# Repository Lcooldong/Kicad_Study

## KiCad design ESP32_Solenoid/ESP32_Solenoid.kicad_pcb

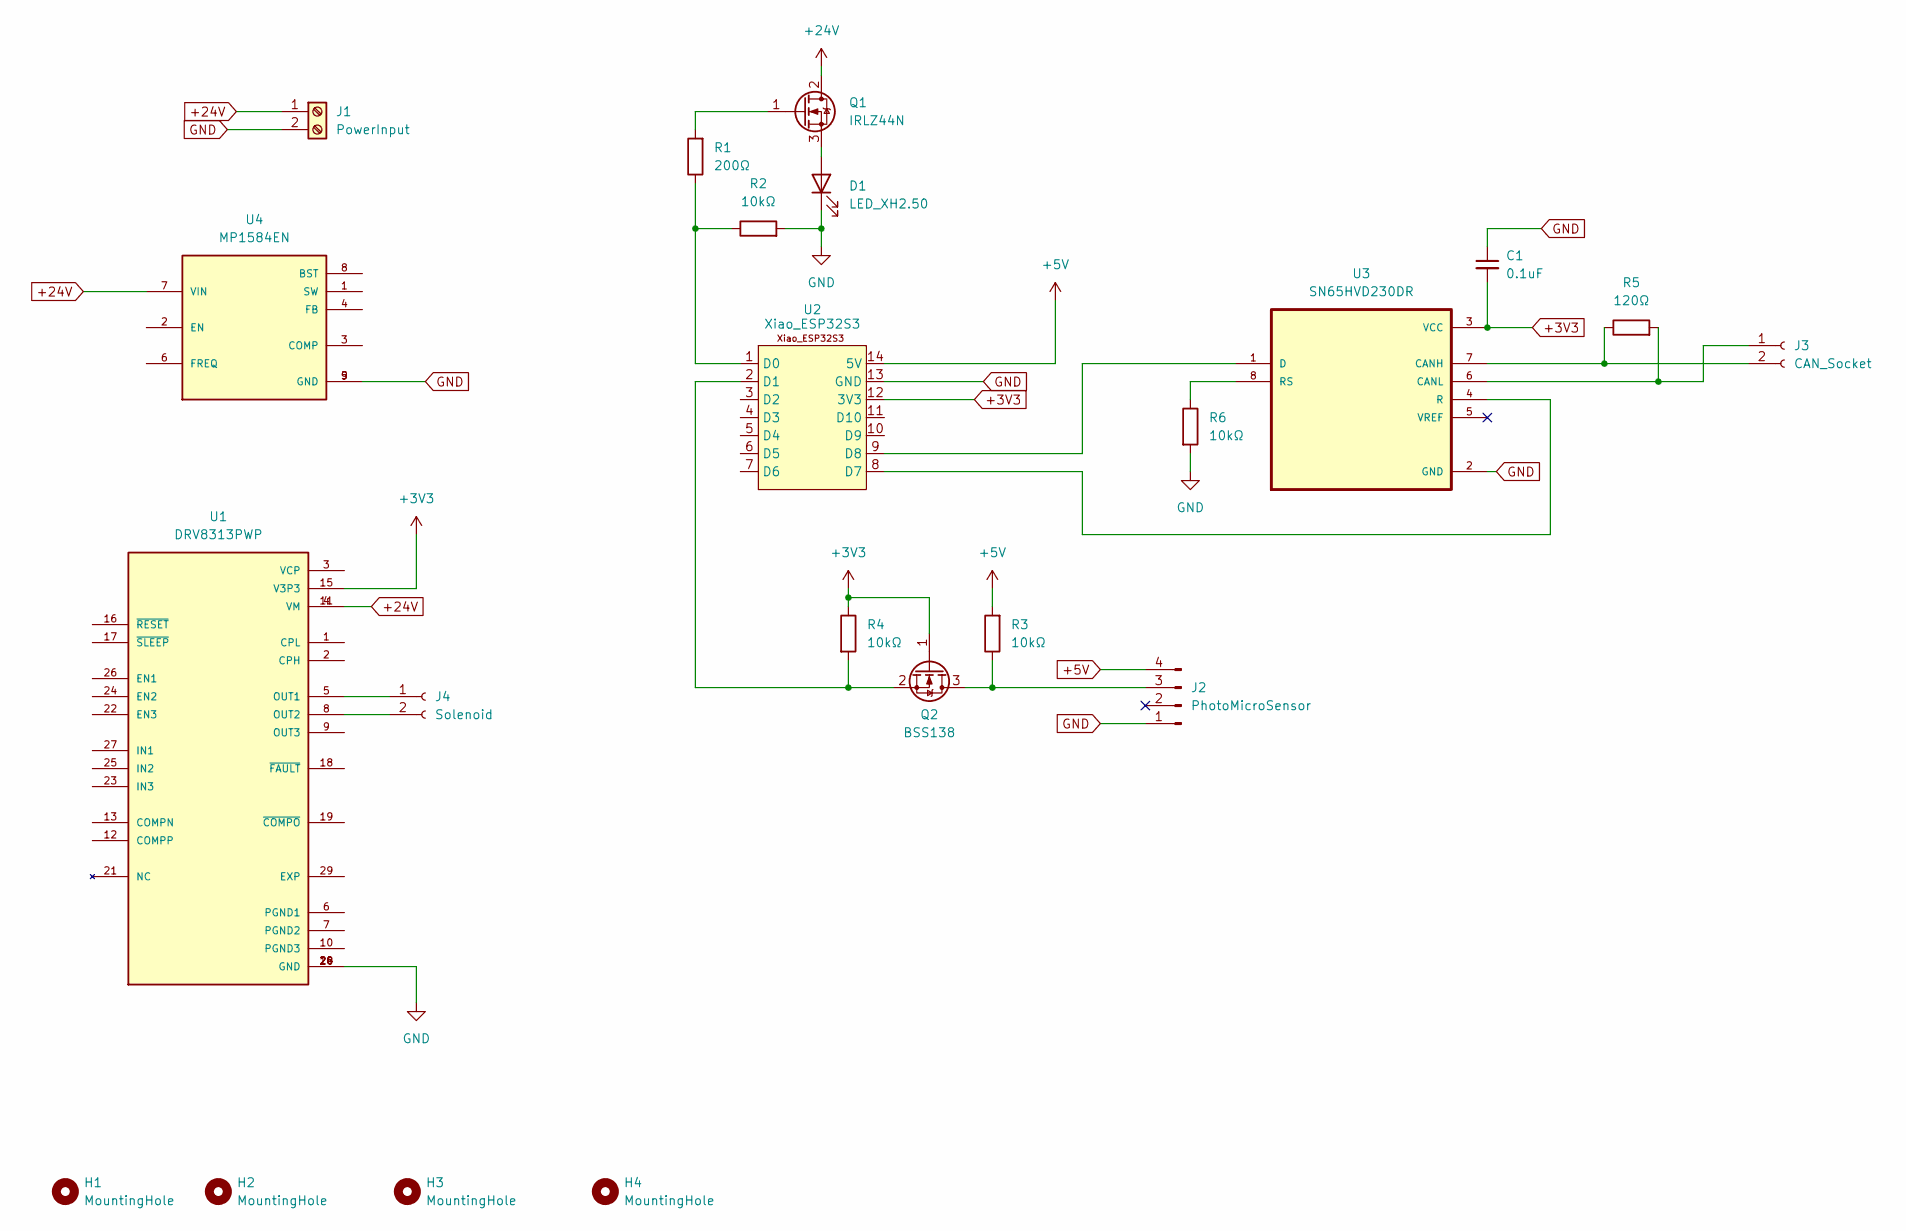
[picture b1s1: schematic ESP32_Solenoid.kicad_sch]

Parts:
C1: 0.1uF; C_1206_3216Metric
D1: LED_XH2.50; JST_XH_B2B-XH-A_1x02_P2.50mm_Vertical
H1, H2, H3, H4: MountingHole; MountingHole_3.2mm_M3_Pad_Via
J1: PowerInput; TerminalBlock_Phoenix_MKDS-1,5-2-5.08_1x02_P5.08mm_Horizont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
J2: PhotoMicroSensor; JST_XH_B4B-XH-A_1x04_P2.50mm_Vertical
J3: CAN_Socket; TerminalBlock_Phoenix_MKDS-1,5-2-5.08_1x02_P5.08mm_Horizont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
J4: Solenoid; TerminalBlock_Phoenix_MKDS-1,5-2-5.08_1x02_P5.08mm_Horizont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
Q1: IRLZ44N; IRLZ44NSTRLPBF
Q2: BSS138; SOT-23
R1: 200Ω; R_1206_3216Metric
R2, R3, R4, R6: 10kΩ; R_1206_3216Metric
R5: 120Ω; R_0805_2012Metric
U1: DRV8313PWP; SOP65P640X120-29N; PARTREV D; DigiKey_Part_Number 296-35540-5-ND
U2: Xiao_ESP32S3; Xiao_ESP32S3_THT
U3: SN65HVD230DR; SN65HVD230DR_SOIC127P599X175-8N
U4: MP1584EN; SOIC127P600X170-9N

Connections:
+3V3: C1.2, Q2.1 (G), R4.1, U1.15 (V3P3), U2.12 (3V3), U3.3 (VCC)
+5V: J2.4, R3.2, U2.14 (5V)
+24V: J1.1, Q1.2 (D), U1.4 (VM), U1.11 (VM), U4.7 (VIN)
GND: C1.1, D1.1 (K), J1.2, J2.1, R2.2, R6.2, U1.14 (GND), U1.20 (GND), U1.28 (GND), U2.13 (GND), U3.2 (GND), U4.5 (GND), U4.9 (GND)
unnamed: D1.2 (A), Q1.3 (S)
unnamed: J2.3, Q2.3 (D), R3.1
unnamed: J3.1, R5.2, U3.6 (CANL)
unnamed: J3.2, R5.1, U3.7 (CANH)
unnamed: J4.1, U1.5 (OUT1)
unnamed: J4.2, U1.8 (OUT2)
unnamed: Q1.1 (G), R1.2
unnamed: Q2.2 (S), R4.2, U2.2 (D1)
unnamed: R1.1, R2.1, U2.1 (D0)
unnamed: U2.8 (D7), U3.4 (R)
unnamed: U2.9 (D8), U3.1 (D)
unnamed: R6.1, U3.8 (RS)

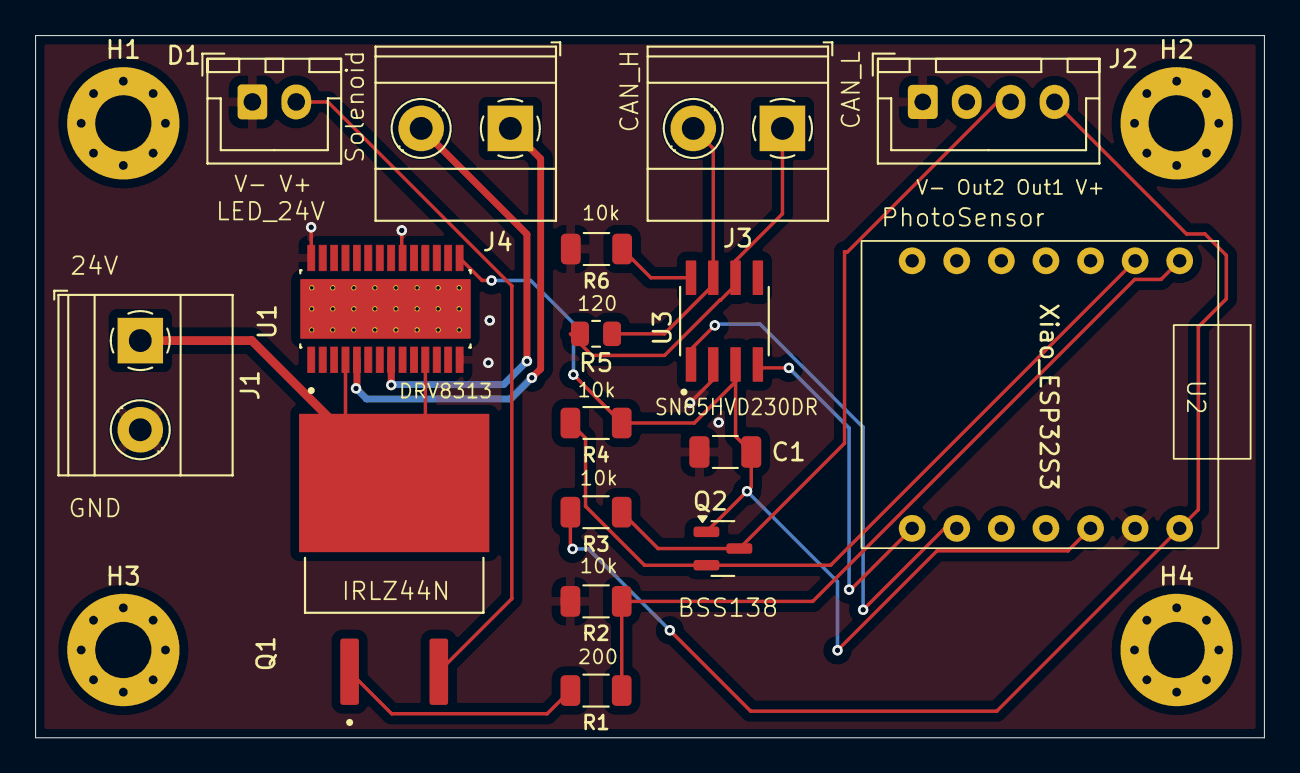
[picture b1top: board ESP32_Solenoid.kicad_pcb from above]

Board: 2 copper layers, 70.0 x 40.0 mm, 21 parts (0 on the bottom side), 16 nets.

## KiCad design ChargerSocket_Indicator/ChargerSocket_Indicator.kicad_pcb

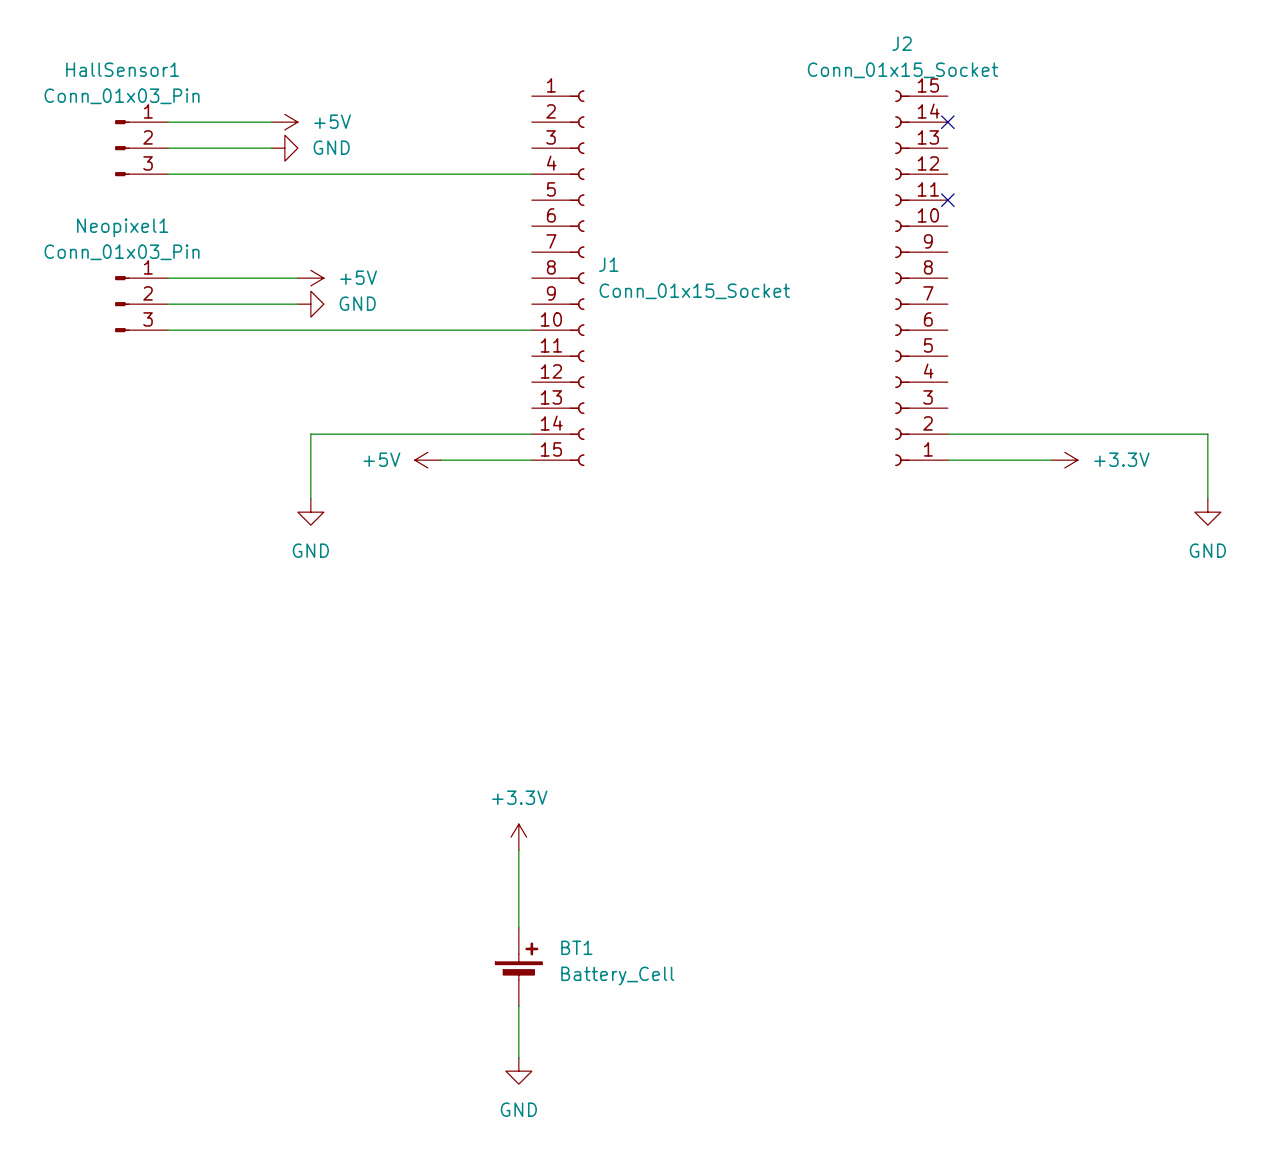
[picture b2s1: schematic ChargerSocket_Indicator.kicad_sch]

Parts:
BT1: Battery_Cell; SolderWire-0.1sqmm_1x02_P3.6mm_D0.4mm_OD1mm_Relief
HallSensor1: Conn_01x03_Pin; PinHeader_1x03_P2.54mm_Vertical
J1, J2: Conn_01x15_Socket; PinSocket_1x15_P2.54mm_Vertical
Neopixel1: Conn_01x03_Pin; PinHeader_1x03_P2.54mm_Vertical

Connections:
+3.3V: BT1.1 (+), J2.1
+5V: HallSensor1.1, J1.15, Neopixel1.1
GND: BT1.2 (-), HallSensor1.2, J1.14, J2.2, Neopixel1.2
unnamed: HallSensor1.3, J1.4
unnamed: J1.10, Neopixel1.3

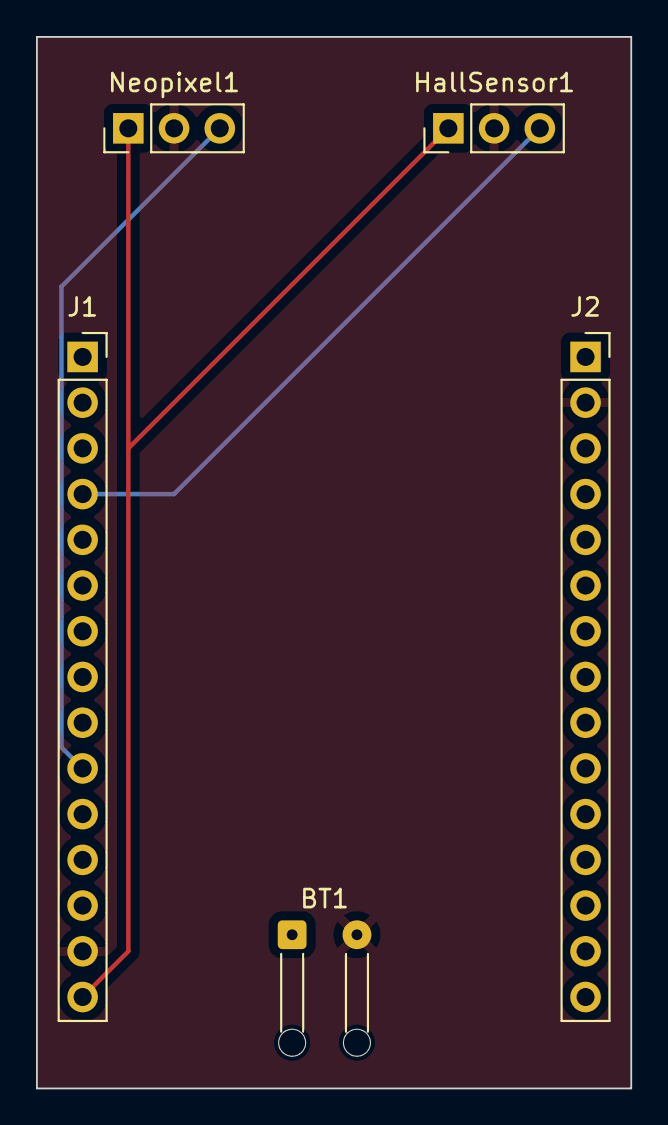
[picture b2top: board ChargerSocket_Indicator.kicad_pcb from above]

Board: 2 copper layers, 33.0 x 58.4 mm, 5 parts (0 on the bottom side), 5 nets.

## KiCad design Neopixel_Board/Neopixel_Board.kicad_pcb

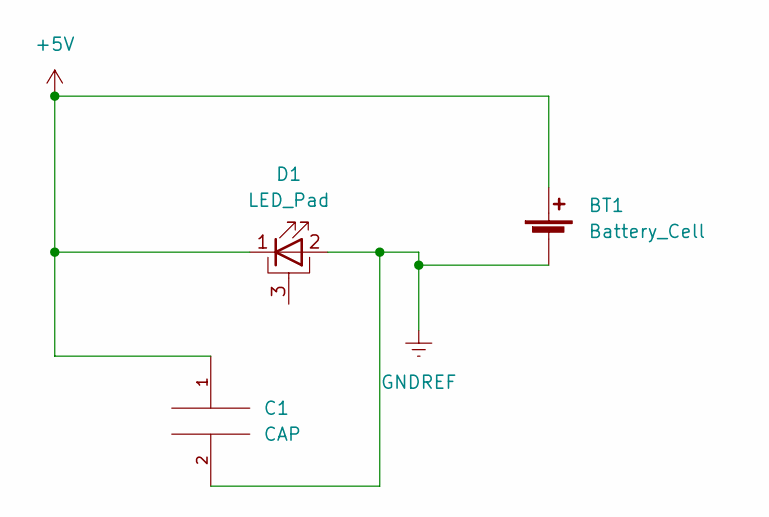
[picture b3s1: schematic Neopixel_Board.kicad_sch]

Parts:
BT1: Battery_Cell; Banana_Jack_2Pin
C1: CAP; CP_Elec_5x3
D1: LED_Pad; LED_WS2812B_PLCC4_5.0x5.0mm_P3.2mm

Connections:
+5V: BT1.1 (+), C1.1, D1.1 (K)
GNDREF: BT1.2 (-), C1.2, D1.2 (A)

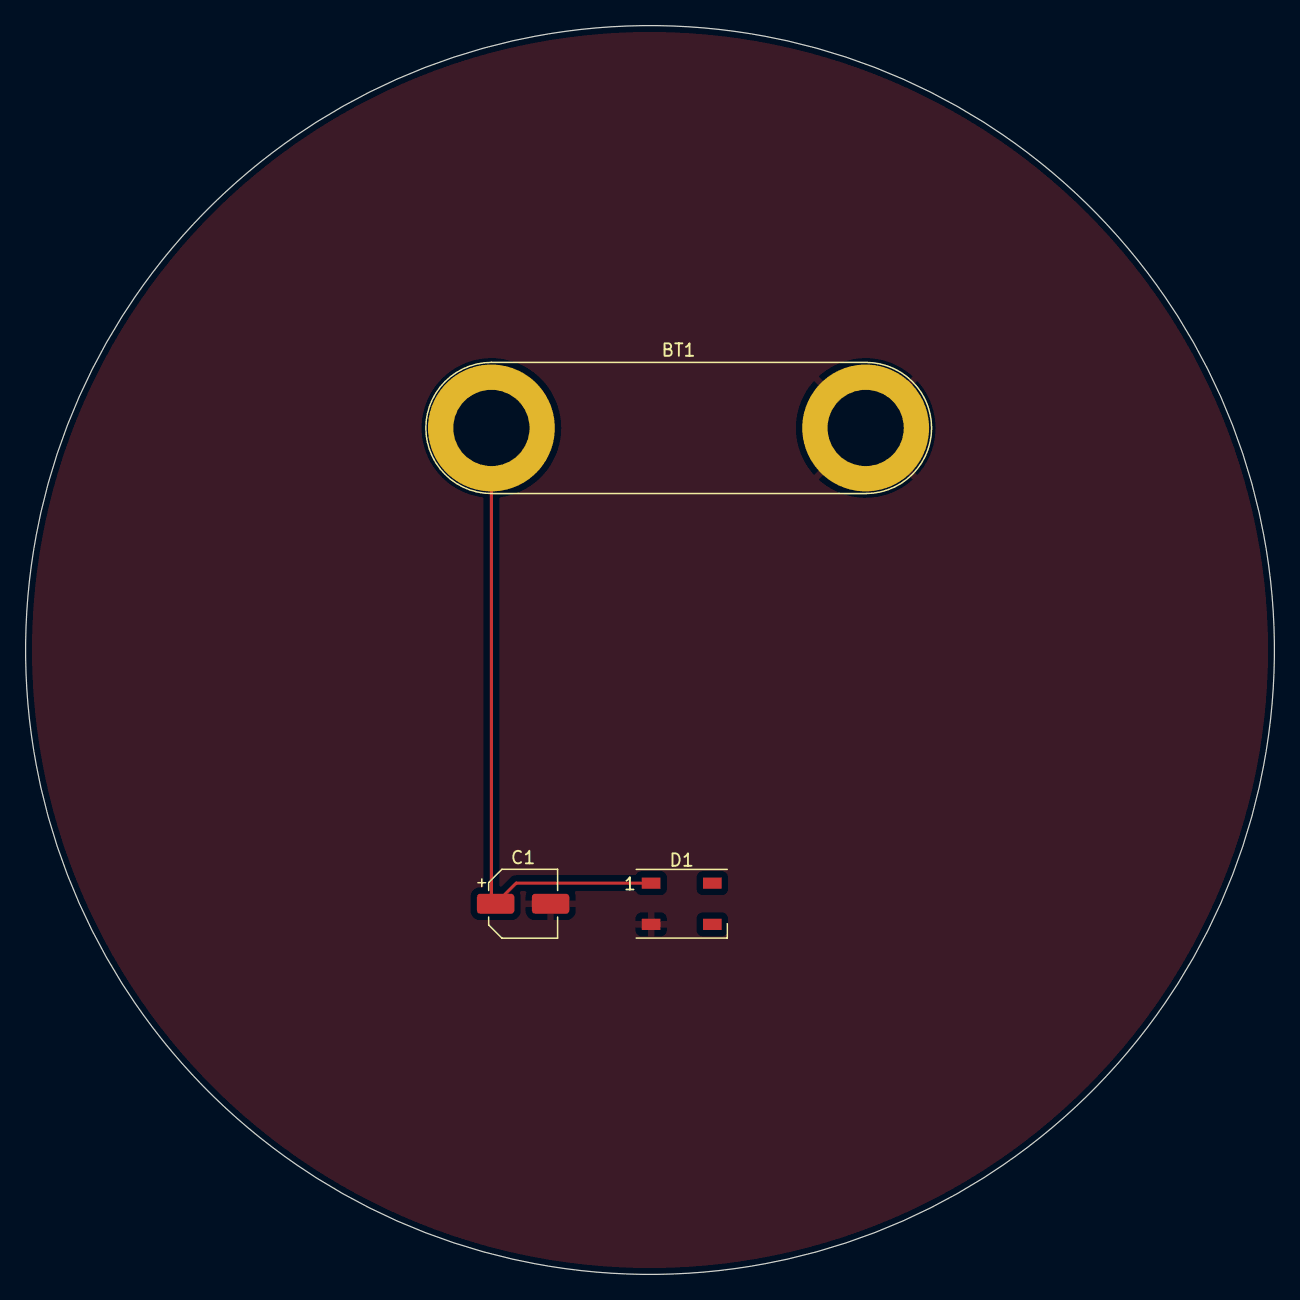
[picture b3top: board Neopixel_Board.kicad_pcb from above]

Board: 2 copper layers, 100.0 x 100.0 mm, 3 parts (0 on the bottom side), 2 nets.

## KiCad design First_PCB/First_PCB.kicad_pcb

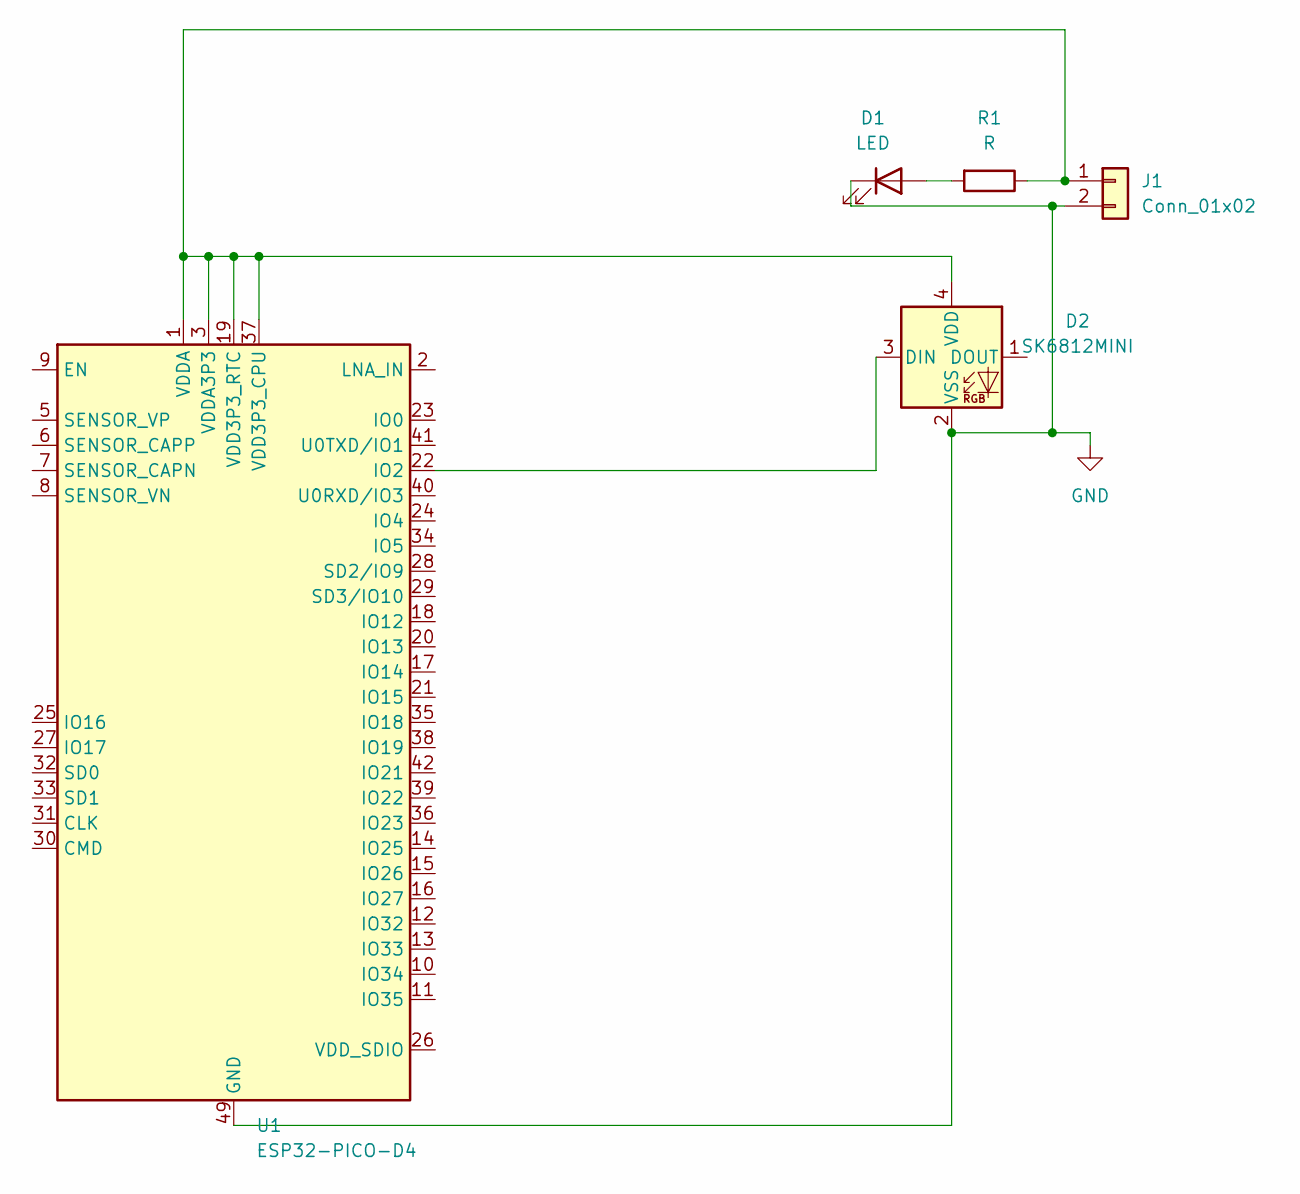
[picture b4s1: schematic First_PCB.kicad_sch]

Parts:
D1: LED; LED_1W_3W_R8
D2: SK6812MINI; LED_SK6812MINI_PLCC4_3.5x3.5mm_P1.75mm
J1: Conn_01x02; PinSocket_1x02_P2.54mm_Vertical
R1: R; R_0603_1608Metric
U1: ESP32-PICO-D4; QFN-48-1EP_7x7mm_P0.5mm_EP5.3x5.3mm

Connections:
GND: D1.1 (K), D2.2 (VSS), J1.2, U1.49 (GND)
unnamed: D1.2 (A), R1.2
unnamed: D2.3 (DIN), U1.22 (IO2)
unnamed: D2.4 (VDD), J1.1, R1.1, U1.1 (VDDA), U1.3 (VDDA3P3), U1.4 (VDDA3P3), U1.19 (VDD3P3_RTC), U1.37 (VDD3P3_CPU), U1.43 (VDDA), U1.46 (VDDA)

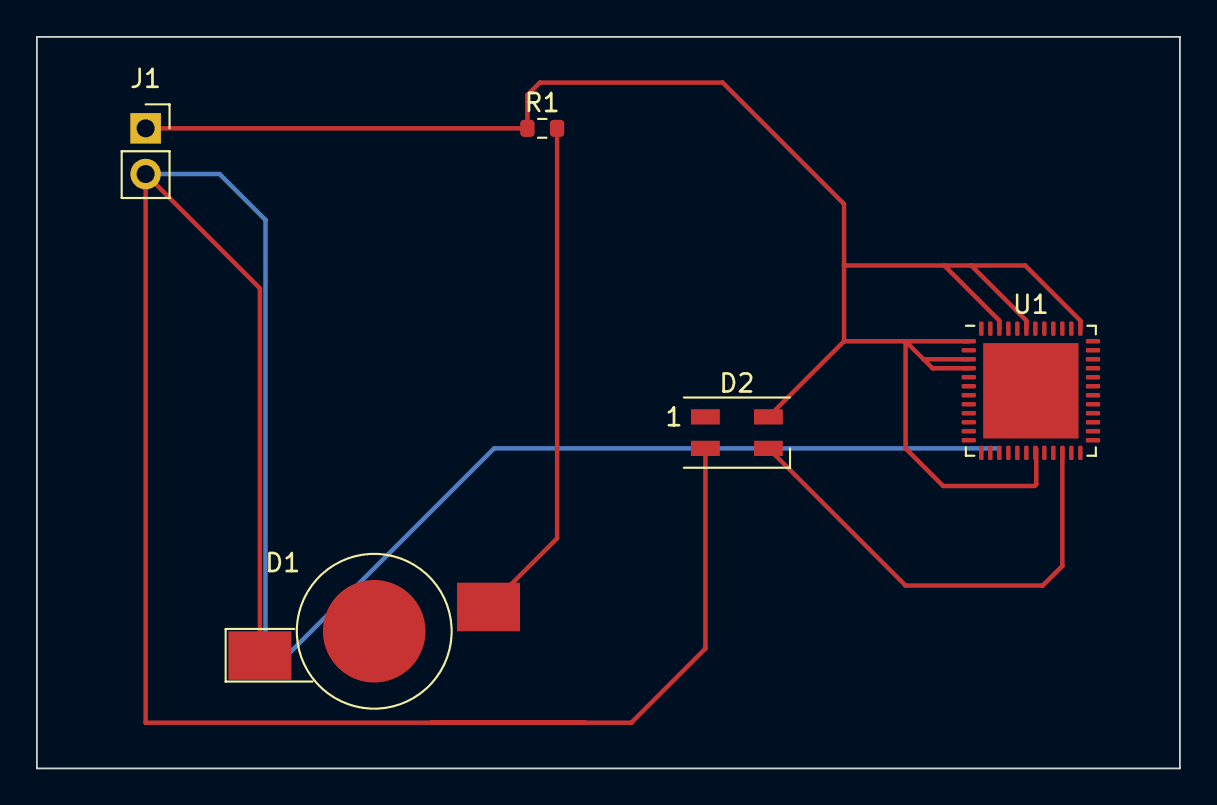
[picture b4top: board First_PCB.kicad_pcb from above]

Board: 2 copper layers, 63.5 x 40.6 mm, 5 parts (0 on the bottom side), 4 nets.

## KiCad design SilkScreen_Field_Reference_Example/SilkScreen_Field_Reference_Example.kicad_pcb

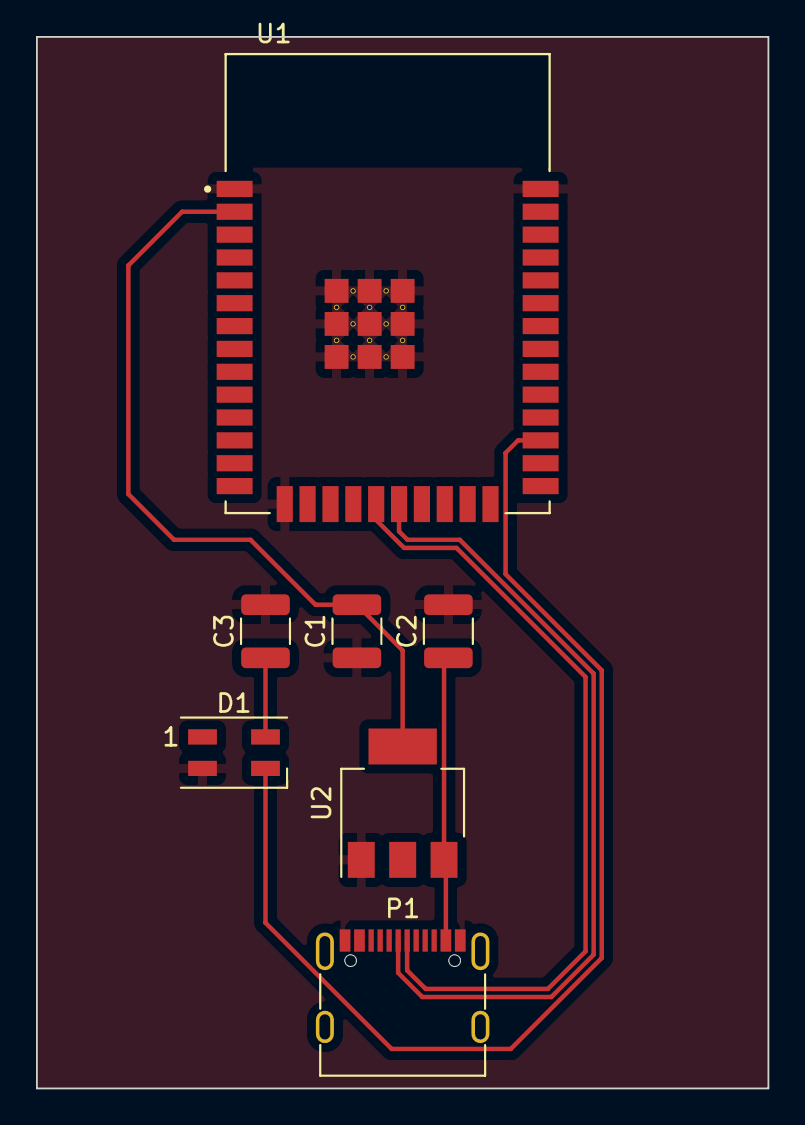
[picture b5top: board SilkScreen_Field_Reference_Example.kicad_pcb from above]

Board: 2 copper layers, 40.6 x 58.4 mm, 7 parts (0 on the bottom side), 6 nets.

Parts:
C1, C2, C3: C; C_1210_3225Metric
D1: SK6812MINI; LED_SK6812MINI_PLCC4_3.5x3.5mm_P1.75mm
P1: USB_C_Plug_USB2.0; USB_C_Receptacle_G-Switch_GT-USB-7010ASV
U1: ESP32-WROOM-32D; MODULE_ESP32-WROOM-32D
U2: AMS1117-3.3; SOT-223-3_TabPin2

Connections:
+5V: C2.1, C3.1, D1.4 (VDD), P1.A4 (VBUS), P1.A9 (VBUS), P1.B4 (VBUS), P1.B9 (VBUS), U2.3 (VI)
GND: C1.1, C2.2, C3.2, D1.2 (VSS), P1.A1 (GND), P1.A12 (GND), P1.B1 (GND), P1.B12 (GND), U1.1 (GND), U1.15 (GND), U1.38 (GND), U1.39_1 (GND), U1.39_2 (GND), U1.39_3 (GND), U1.39_4 (GND), U1.39_5 (GND), U1.39_6 (GND), U1.39_7 (GND), U1.39_8 (GND), U1.39_9 (GND), U1.39_10 (GND), U1.39_11 (GND), U1.39_12 (GND), U1.39_13 (GND), U1.39_14 (GND), U1.39_15 (GND), U1.39_16 (GND), U1.39_17 (GND), U1.39_18 (GND), U1.39_19 (GND), U1.39_20 (GND), U1.39_21 (GND), U2.1 (GND)
unnamed: D1.3 (DIN), U1.27 (IO16)
unnamed: P1.A6 (D+), U1.20 (SCK/CLK)
unnamed: P1.A7 (D-), U1.19 (SCS/CMD)
unnamed: C1.2, U1.2 (3V3), U2.2 (VO)
